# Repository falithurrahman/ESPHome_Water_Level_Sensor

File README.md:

### Description
In this repository, i share my project on making water level sensor integrated with home assistant. The controller for this water level sensor is running on ESPHome Firmware. I will explain the details of this project below.

#### Tools and Equipment
  - Wemos D1 Mini
  - DC 5V Power Supply
  - Relay Optocoupler <br>
    This relay will be connected to water pump so that we will be able to autonomously turn the pump on and off. 
  - Ultrasonic Distance Sensor <br>
    There are various kind of this sensor like SRF04, HC-SR04, US-100. You can use any kind of sensor of your desire. They all are working on same principle.

#### Wiring Diagram
Here is the wiring diagram between WemosD1 Mini and Relay Optocoupler. <br>
| Wemos D1 Mini      | Relay Optocoupler |
| ----------- | ----------- |
| VCC         | VCC       |
| GND         | GND        |
|D8|Input|

Here is the wiring diagram between WemosD1 Mini and Ultrasonic Distance Sensor. <br>
| Wemos D1 Mini      | Ultrasonic Distance Sensor |
| ----------- | ----------- |
| VCC         | VCC       |
| GND         | GND        |
|D3|Trig|
|D4|Echo|

I have provided you the schematic and board file inside control board folder. The filename is WemosD1_Control. It will ease you to understand wiring diagram of the circuit.

#### Code
Since i use ESPHome firmware running on my Wemos D1 Mini, i write the code in yaml file. You can peek the code in this repository with WemosD1.yaml filename. The main part of the code is within the sensor and switch part. For pin mapping, we can use whether with D8, D3, D4 syntax or GPIO2, GPIO0, GPIO15 syntax. Both of them work fine.

````yaml
sensor:
  - platform: ultrasonic
    trigger_pin: GPIO0
    echo_pin: GPIO2
    name: "Ultrasonic Sensor"
    update_interval: 10s
    timeout: 4.0m
    filters:
    - lambda: return (1-x);
    unit_of_measurement: "meter"
    
switch:
  - platform: gpio
    name: "Kendali Pompa Air"
    id: kendali_pompa_air
    pin:
      number: GPIO15
      inverted: True
````

In filters, i inverse the distance result from sensor. It's because i place ultrasonic distance sensor on the top of my water tank, facing down the water tank. As the water rise, the tank will be full. But the ultrasonic distance sensor reading will get shorter. Then, i inverse sensor reading so that as the water rise, it'll also tell us that the tank is getting full.

#### Automation
The idea of using home assistant is because i want to add automation in this project. By using automation, i can have the water pump to turn on and off, filling water tank autonomously. The trigger of this automation is based on ultrasonic sensor reading. You can peek the automation code in this repository with automation.yaml filename. 

````yaml
  alias: PompaAir_TurnOn_Auto
  description: ''
  trigger:
  - above: 0
    below: 0.2
    device_id: 1c657803e15f46eebff68046b731fd01
    domain: sensor
    entity_id: sensor.ultrasonic_sensor
    for:
      hours: 0
      minutes: 0
      seconds: 5
    platform: device
    type: value
````
As you can see part of the automation.yaml i copy, trigger to turn on the water pump is the inverted result from ultrasonic distance reading. If the value shows between 0 to 0.2 meters, it will turn on water pump.
````yaml
  alias: PompaAir_TurnOff_Auto
  description: ''
  trigger:
  - above: 0.8
    device_id: 1c657803e15f46eebff68046b731fd01
    domain: sensor
    entity_id: sensor.ultrasonic_sensor
    for:
      hours: 0
      minutes: 0
      seconds: 10
    platform: device
    type: value
````
But if the value shows between 0.8 meter, it will turn on water pump. Why not use 1 meter? Because the height of my water tank is 1m. If the pump stop by 1m, it will make the sensor sink and i don't want it happen.

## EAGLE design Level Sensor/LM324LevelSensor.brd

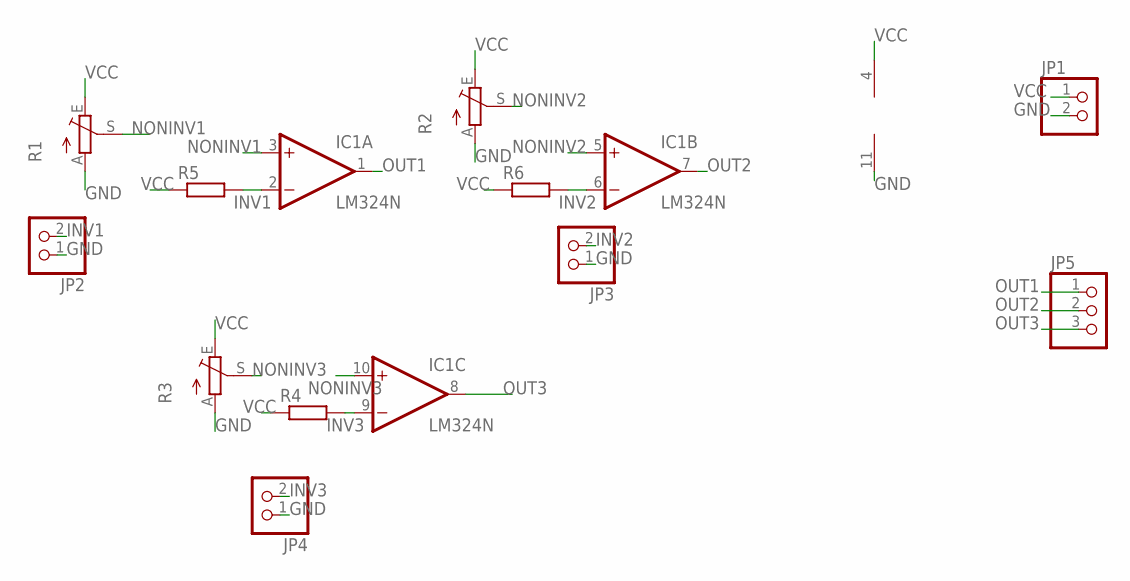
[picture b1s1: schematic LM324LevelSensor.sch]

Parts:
IC1: LM324N; DIL14
JP1, JP2, JP3, JP4: PINHD-1X2; 1X02
JP5: PINHD-1X3; 1X03
R1, R2, R3: TRIM_EU-B25P; B25P
R4, R5, R6: R-EU_0204/7; 0204/7

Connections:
GND: IC1.11 (V-), JP1.2, JP2.1, JP3.1, JP4.1, R1.A, R2.A, R3.A
INV1: IC1.2 (-IN), JP2.2, R5.2
INV2: IC1.6 (-IN), JP3.2, R6.2
INV3: IC1.9 (-IN), JP4.2, R4.2
NONINV1: IC1.3 (+IN), R1.S
NONINV2: IC1.5 (+IN), R2.S
NONINV3: IC1.10 (+IN), R3.S
OUT1: IC1.1 (OUT), JP5.1
OUT2: IC1.7 (OUT), JP5.2
OUT3: IC1.8 (OUT), JP5.3
VCC: IC1.4 (V+), JP1.1, R1.E, R2.E, R3.E, R4.1, R5.1, R6.1

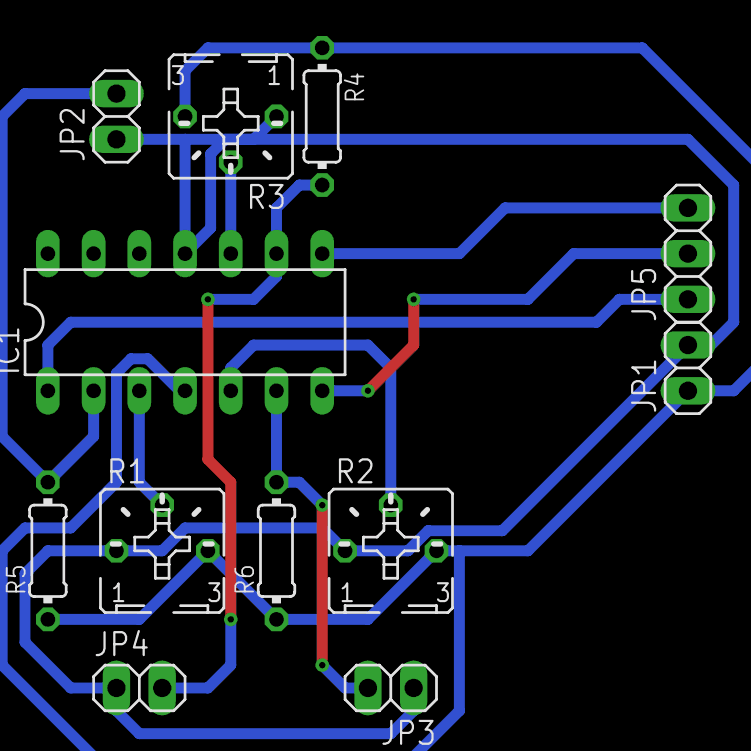
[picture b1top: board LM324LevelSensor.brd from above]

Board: 2 copper layers, 12 parts (0 on the bottom side), 11 nets.

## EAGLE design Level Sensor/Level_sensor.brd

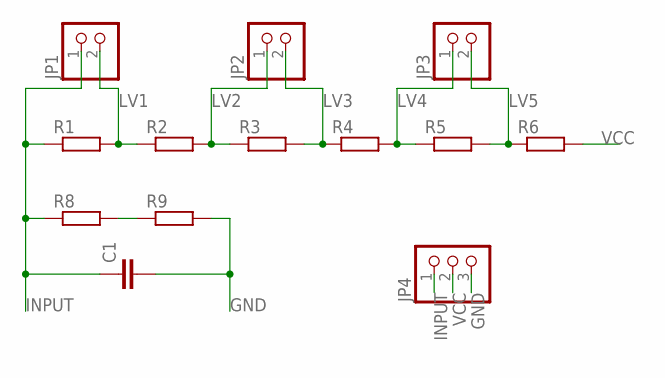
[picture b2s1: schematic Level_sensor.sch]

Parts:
C1: C-EU025-030X050; C025-030X050
JP1, JP2, JP3: PINHD-1X2; 1X02
JP4: PINHD-1X3; 1X03
R1, R2, R3, R4, R5, R6, R8, R9: R-EU_0204/7; 0204/7

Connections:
GND: C1.2, JP4.3, R9.2
INPUT: C1.1, JP1.1, JP4.1, R1.1, R8.1
LV1: JP1.2, R1.2, R2.1
LV2: JP2.1, R2.2, R3.1
LV3: JP2.2, R3.2, R4.1
LV4: JP3.1, R4.2, R5.1
LV5: JP3.2, R5.2, R6.1
unnamed: R8.2, R9.1
VCC: JP4.2, R6.2

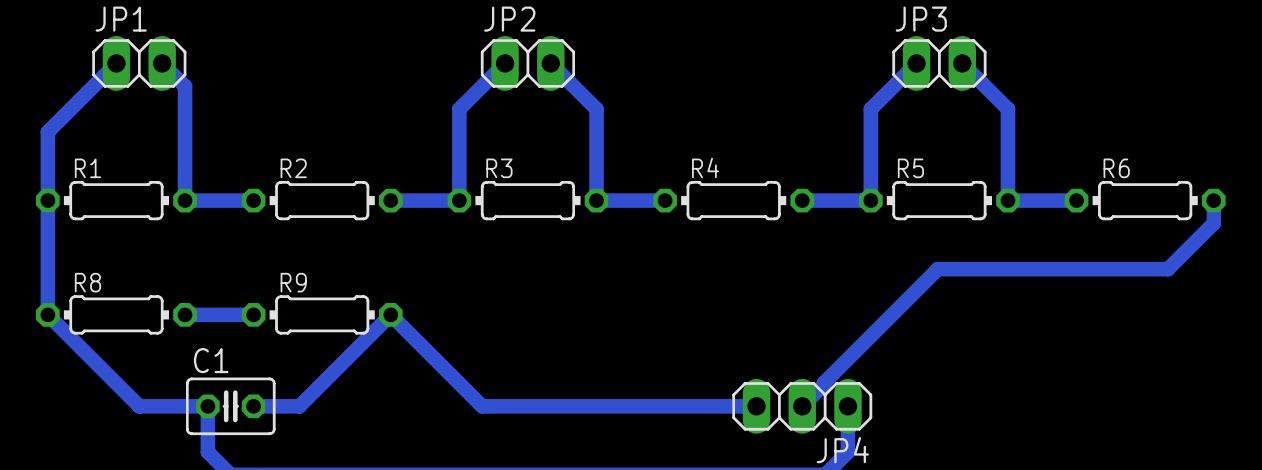
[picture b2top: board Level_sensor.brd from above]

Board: 2 copper layers, 13 parts (0 on the bottom side), 9 nets.

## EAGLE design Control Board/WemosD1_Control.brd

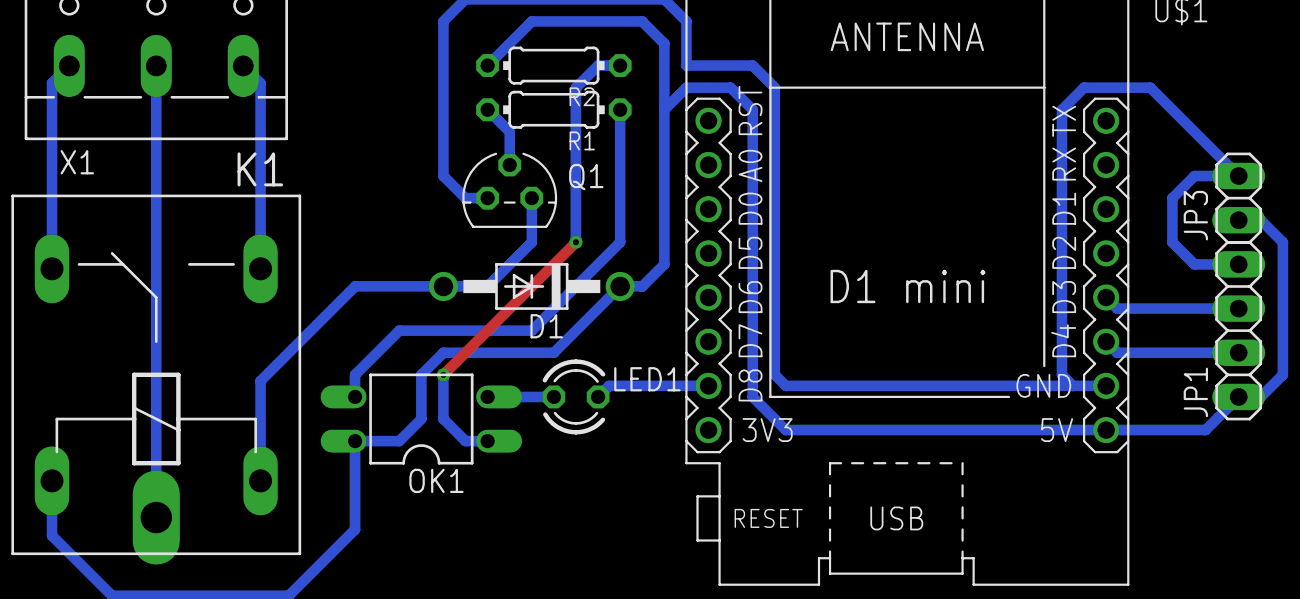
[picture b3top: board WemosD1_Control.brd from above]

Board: 2 copper layers, 11 parts (0 on the bottom side), 13 nets.

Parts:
D1: 1N4004; DO41-10
JP1: 1X04
JP3: 1X02
K1: ZF112
LED1: LED3MM
OK1: PC817; DIL04
Q1: 2N3904; TO92
R1, R2: 0204/7
U$1: WEMOS-D1-MINI
X1: W237-103

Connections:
COM: K1.P, X1.2
ECHO: JP1.2, U$1.JP2.6
GND: JP1.4, JP3.2, Q1.3, U$1.JP2.7
IN1: LED1.K, U$1.JP1.7
unnamed: D1.A, K1.2, Q1.1
unnamed: OK1.3, R1.1
unnamed: Q1.2, R1.2
unnamed: LED1.A, OK1.2
unnamed: OK1.1, R2.1
NC: K1.O, X1.1
NO: K1.S, X1.3
TRIG: JP1.3, U$1.JP2.5
VCC: D1.C, JP1.1, JP3.1, K1.1, OK1.4, R2.2, U$1.JP2.8

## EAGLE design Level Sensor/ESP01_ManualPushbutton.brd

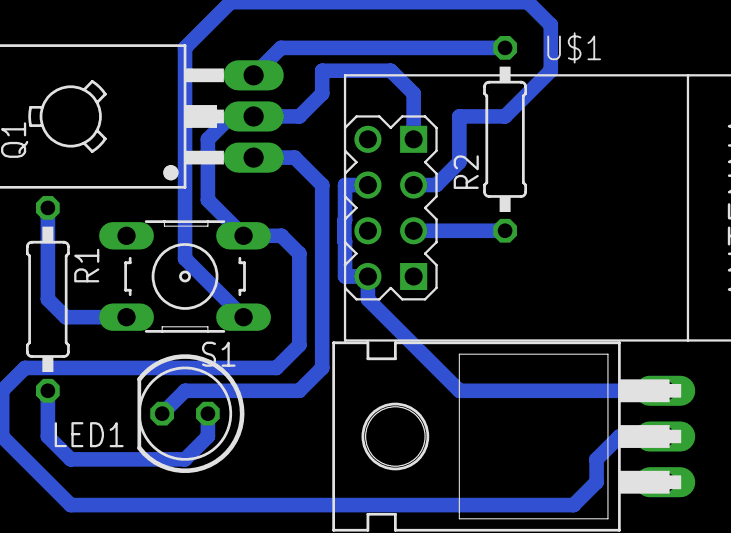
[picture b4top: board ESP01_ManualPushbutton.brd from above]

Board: 2 copper layers, 7 parts (0 on the bottom side), 6 nets.

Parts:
IC1: 7805T; TO220H
LED1: LED5MM
Q1: BD140; TO126
R1, R2: 0207/10
S1: B3F-10XX
U$1: WIRELESS-WIFI-ESP-01

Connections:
GND: IC1.2, Q1.2, S1.3, S1.4, U$1.A1
INDIKATOR: R2.1, U$1.C1
unnamed: Q1.3, R2.2
unnamed: LED1.K, Q1.1
PUSHBUTTON: R1.1, S1.1, S1.2, U$1.B1
VCC: IC1.3, LED1.A, R1.2, U$1.B2, U$1.D2

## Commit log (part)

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2020-04-13 Add sensor board and schematic file
    This sensor is used for detecting water level based on resistance change
2020-04-13 Add sensor simulation file
2020-04-14 Add WemosD1 code file
2020-04-14 Disable moving average filter
2020-04-15 Add linear calibration
2020-04-15 Add linear calibration in WemosD1.yaml
2020-04-15 Add LM324 Level Sensor board and schematic
2020-04-16 Change to ultrasonic distance sensor
2020-04-18 Add automation file
2020-04-18 Add WemosD1_Control Board
2020-04-18 Change device name and remove unnecessary comments
2020-04-18 Add ESP01_ManualPushbutton board
2020-04-18 Create specific folder for ESP Controller Boards
2020-04-18 Add automations to control PompaAir through ESP01_ManualPushbutton
2020-04-19 Edit VSCode configuration file
2020-05-01 Add description in readme file
2020-05-01 Add tools and equipment in readme file
2020-05-01 Add wiring diagram in readme file
2020-05-01 Edit sensor pin and add filter in WemosD1.yaml file
2020-05-01 Add code in readme file
2020-05-01 Edit code in readme file
2020-05-01 Add automation in readme file
2020-05-02 Move automation and wemosd1 yaml file to code folder

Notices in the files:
parts and their libraries:
diy-modules: Released under the Creative Commons Attribution 4.0 International License: http://creativecommons.org/licenses/by/4.0
